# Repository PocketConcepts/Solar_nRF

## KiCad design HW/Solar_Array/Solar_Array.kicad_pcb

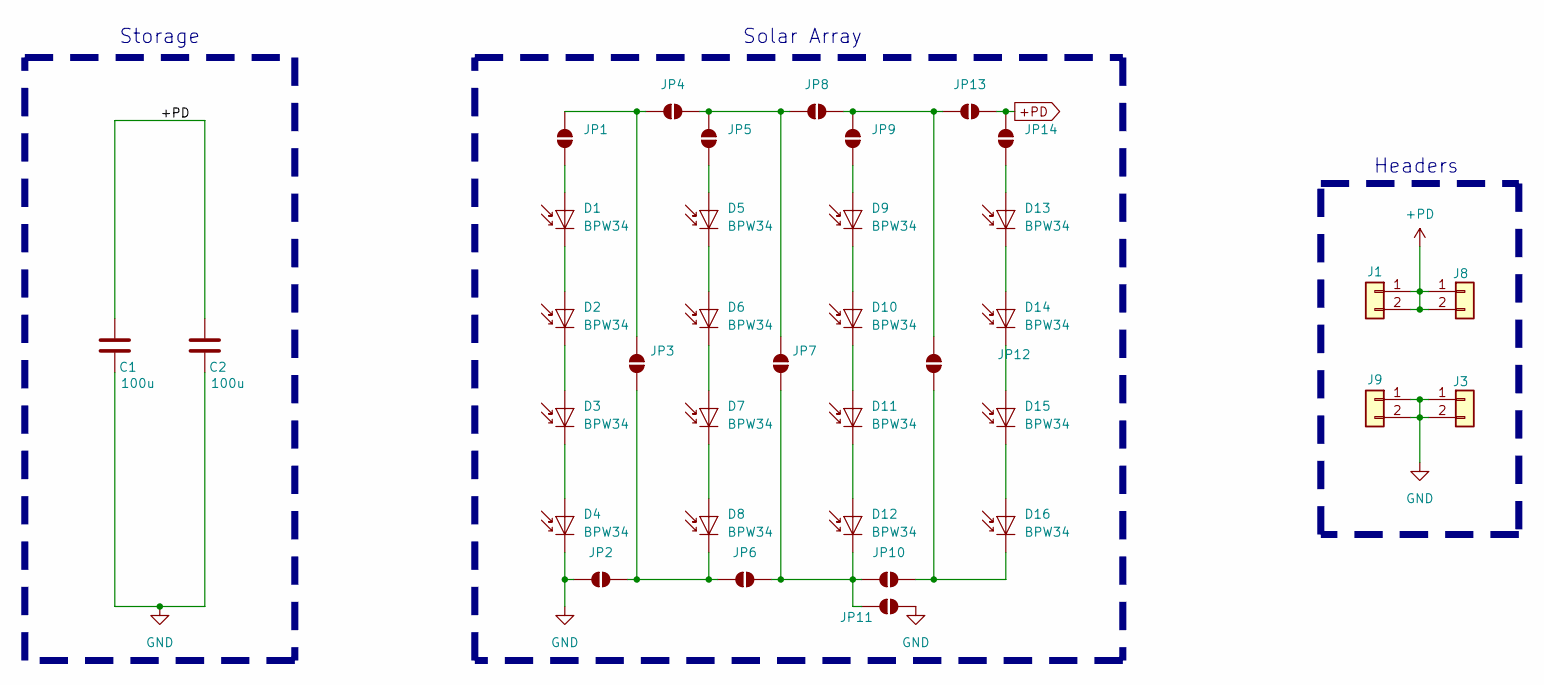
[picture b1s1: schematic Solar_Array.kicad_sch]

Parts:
C1, C2: 100u; C_1210_3225Metric_Pad1.33x2.70mm_HandSolder
D1, D2, D3, D4, D5, D6, D7, D8, D9, D10, D11, D12, D13, D14, D15, D16: BPW34; Osram_DIL2_4.3x4.65mm_P5.08mm
J1, J3, J8, J9: Conn_01x02; PinSocket_1x02_P2.54mm_Vertical
JP1, JP2, JP3, JP4, JP5, JP6, JP7, JP8, JP9, JP10, JP11, JP12, JP13, JP14: SolderJumper_2_Open; SolderJumper-2_P1.3mm_Open_RoundedPad1.0x1.5mm

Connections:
+PD: C1.1, C2.1, J1.1, J1.2, J8.1, J8.2, JP13.1 (A), JP14.2 (B)
GND: C1.2, C2.2, D4.1 (K), J3.1, J3.2, J9.1, J9.2, JP2.2 (B), JP11.1 (A)
unnamed: D1.2 (A), JP1.1 (A)
unnamed: D1.1 (K), D2.2 (A)
unnamed: D2.1 (K), D3.2 (A)
unnamed: D3.1 (K), D4.2 (A)
unnamed: D5.2 (A), JP5.1 (A)
unnamed: D5.1 (K), D6.2 (A)
unnamed: D6.1 (K), D7.2 (A)
unnamed: D7.1 (K), D8.2 (A)
unnamed: D8.1 (K), JP2.1 (A), JP3.1 (A), JP6.2 (B)
unnamed: D9.2 (A), JP9.1 (A)
unnamed: D9.1 (K), D10.2 (A)
unnamed: D10.1 (K), D11.2 (A)
unnamed: D11.1 (K), D12.2 (A)
unnamed: D12.1 (K), JP6.1 (A), JP7.1 (A), JP10.2 (B), JP11.2 (B)
unnamed: D13.2 (A), JP14.1 (A)
unnamed: D13.1 (K), D14.2 (A)
unnamed: D14.1 (K), D15.2 (A)
unnamed: D15.1 (K), D16.2 (A)
unnamed: D16.1 (K), JP10.1 (A), JP12.1 (A)
unnamed: JP1.2 (B), JP3.2 (B), JP4.2 (B)
unnamed: JP4.1 (A), JP5.2 (B), JP7.2 (B), JP8.2 (B)
unnamed: JP8.1 (A), JP9.2 (B), JP12.2 (B), JP13.2 (B)

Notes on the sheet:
Solar Array
Storage
Headers

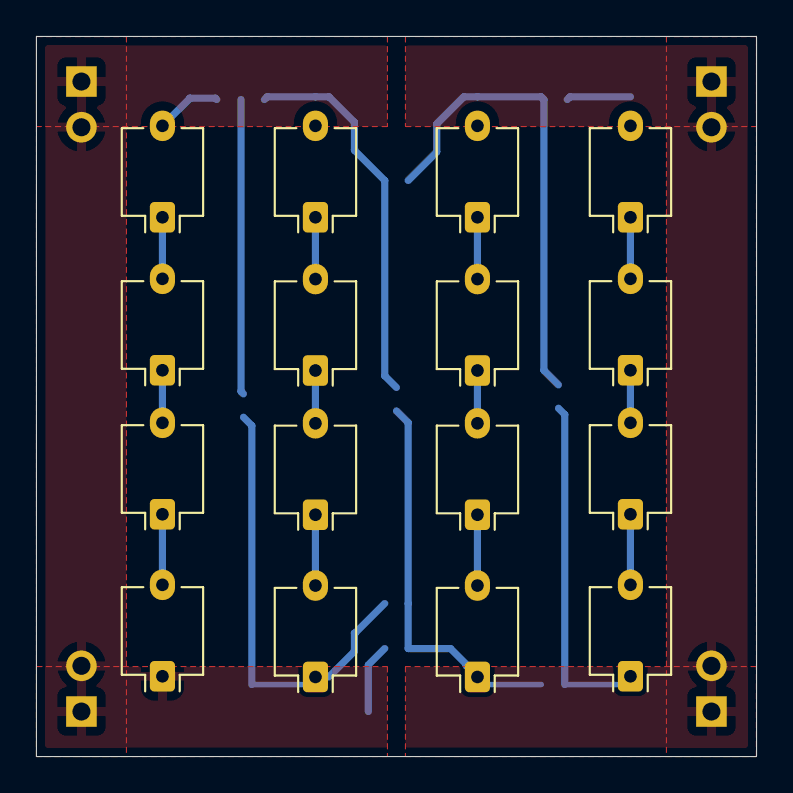
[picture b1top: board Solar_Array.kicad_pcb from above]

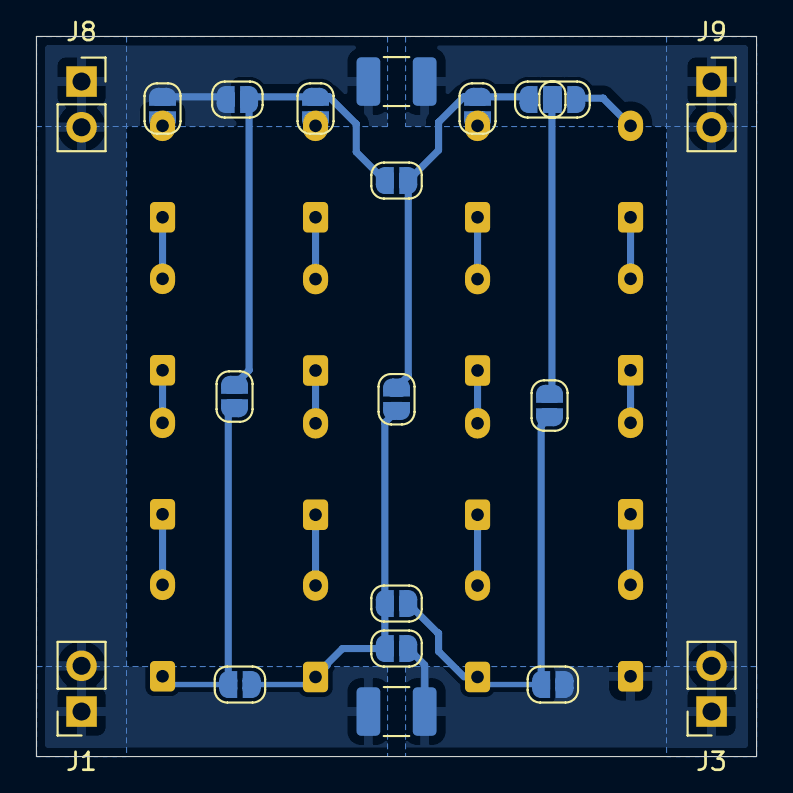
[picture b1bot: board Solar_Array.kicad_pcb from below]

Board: 2 copper layers, 40.0 x 40.0 mm, 36 parts (20 on the bottom side), 24 nets.

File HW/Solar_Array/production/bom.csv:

Designator,Footprint,Quantity,Value,LCSC Part #
"C1, C2",1210,2,100u,
"D1, D10, D11, D12, D13, D14, D15, D16, D2, D3, D4, D5, D6, D7, D8, D9",Osram_DIL2_4.3x4.65mm_P5.08mm,16,BPW34,
"J1, J3, J8, J9",PinSocket_1x02_P2.54mm_Vertical,4,Conn_01x02,

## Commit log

2026-05-14 Fixed solar array copper pours and component links. Regenerated production data.
